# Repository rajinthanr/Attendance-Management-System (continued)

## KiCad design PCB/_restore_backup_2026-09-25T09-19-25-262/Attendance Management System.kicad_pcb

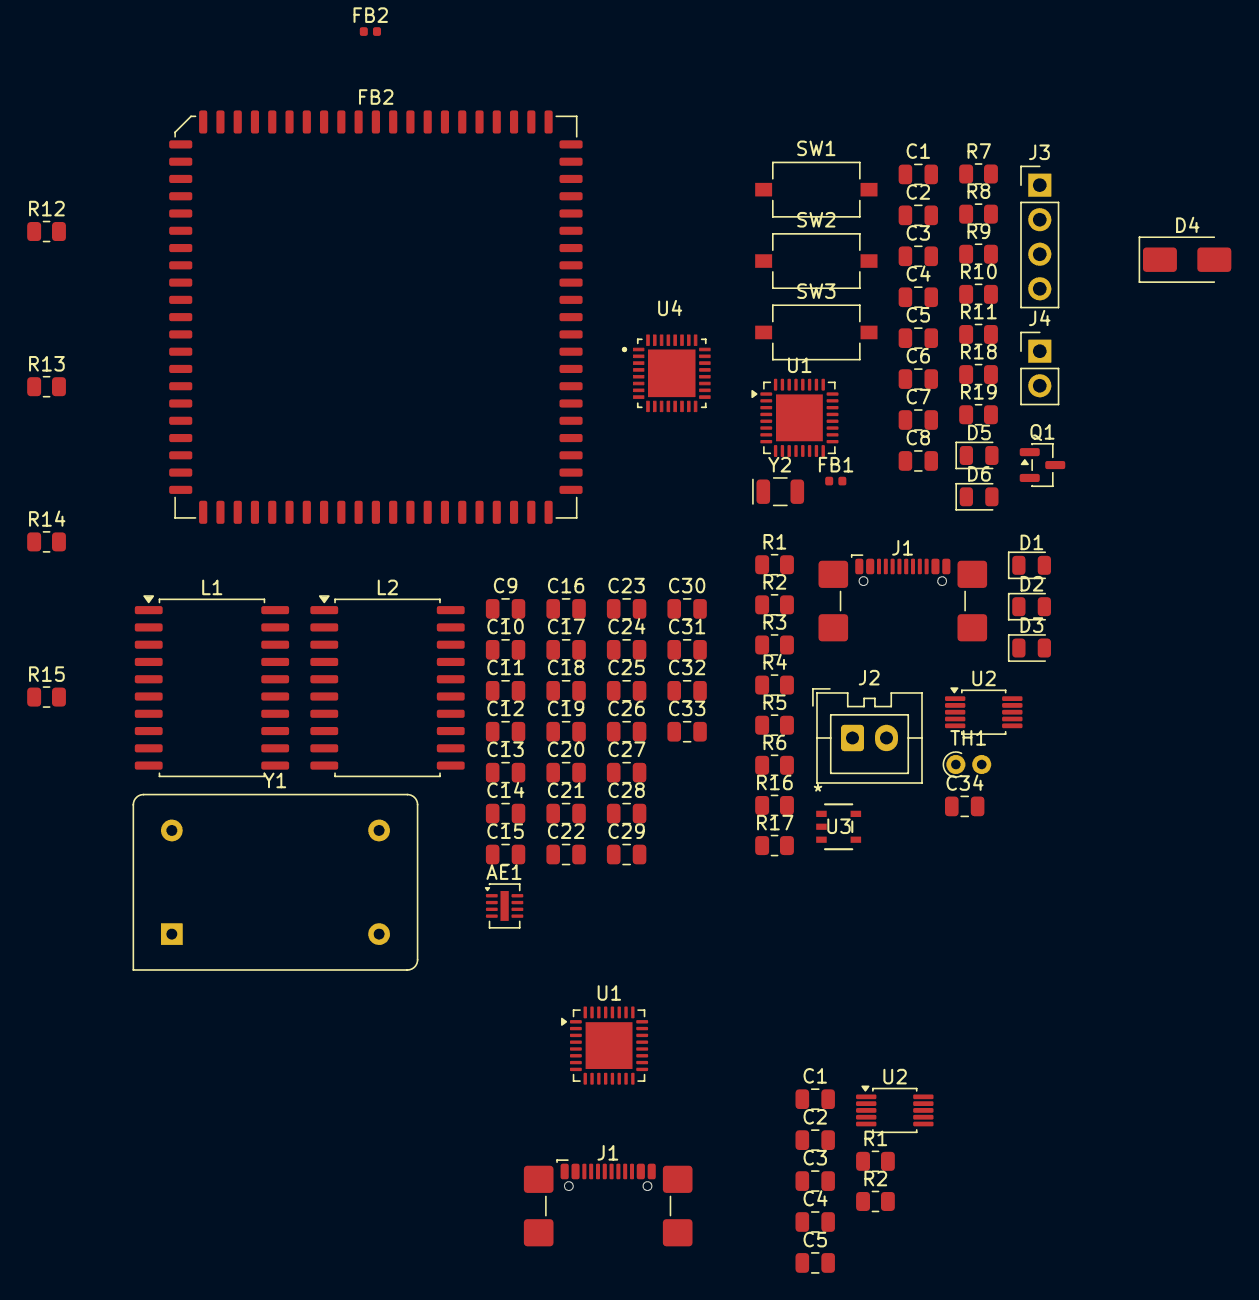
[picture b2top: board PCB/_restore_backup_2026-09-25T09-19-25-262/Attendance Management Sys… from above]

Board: 2 copper layers, 90 parts (0 on the bottom side), 59 nets, no tracks yet.

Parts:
AE1: Antenna; DFN-8-1EP_2x3mm_P0.5mm_EP0.61x2.2mm
C1, C1#2, C3, C3#2, C8, C34: 100n; C_0805_2012Metric
C2, C2#2: 4.7u; C_0805_2012Metric
C4, C4#2: 10n; C_0805_2012Metric
C5, C5#2: 1u; C_0805_2012Metric
C6, C7: 4.3p; C_0805_2012Metric
C9, C10: 15pF; C_0805_2012Metric
C11, C24, C25: 100nF; C_0805_2012Metric
C12, C13: 150 pF; C_0805_2012Metric
C14, C15: 100 pF; C_0805_2012Metric
C16, C17: 68 pF; C_0805_2012Metric
C18, C19: 270 pF; C_0805_2012Metric
C20, C21: 10uF; C_0805_2012Metric
C22, C23, C28, C29, C30: 100 nF; C_0805_2012Metric
C26, C27, C31, C32: 2.2uF; C_0805_2012Metric
C33: 1 uF; C_0805_2012Metric
D1, D5: RED; LED_0805_2012Metric
D2, D3, D6: GREEN; LED_0805_2012Metric
D4: SS14; D_SMA
FB1, FB2#2: FB 600 Ohm @ 100MHz; L_0402_1005Metric
FB2: 600 Ohm @ 100MHz; PLCC-84_29.3x29.3mm_P1.27mm
J1, J1#2: USB_C_Receptacle_USB2.0_16P; USB_C_Receptacle_GCT_USB4110
J2: BAT; JST_XA_B02B-XASK-1_1x02_P2.50mm_Vertical
J3: SW; PinHeader_1x04_P2.54mm_Vertical
J4: MOT; PinHeader_1x02_P2.54mm_Vertical
L1, L2: 470 nH; SOIC-20W_7.5x12.8mm_P1.27mm
Q1: AO3400A; SOT-23
R1, R1#2, R2, R2#2: 5K1; R_0805_2012Metric
R3, R4, R5, R9, R10: 470; R_0805_2012Metric
R6: 1K; R_0805_2012Metric
R7, R8, R11: 10K; R_0805_2012Metric
R12: 10k; R_0805_2012Metric
R13, R14: 1 KOhm; R_0805_2012Metric
R15: 1.5 KOhm; R_0805_2012Metric
R16, R18, R19: 4M7; R_0805_2012Metric
R17: 2M7; R_0805_2012Metric
SW1: RST; SW_Tactile_SPST_NO_Straight_CK_PTS636Sx25SMTRLFS
SW2: BOOT; SW_Tactile_SPST_NO_Straight_CK_PTS636Sx25SMTRLFS
SW3: KEY; SW_Tactile_SPST_NO_Straight_CK_PTS636Sx25SMTRLFS
TH1: Therm_NTC; R_Axial_DIN0204_L3.6mm_D1.6mm_P1.90mm_Vertical
U1, U1#2: STM32L432KCUx; QFN-32-1EP_5x5mm_P0.5mm_EP3.45x3.45mm
U2, U2#2: MCP73833-xxx-UN; MSOP-10_3x3mm_P0.5mm
U3: TPS7A0233PDBVR; SOT23_DBV_TEX-L
U4: ST25R3916-AQWT; QFN50P500X500X100-33N
Y1: 27.120 MHz; Oscillator_DIP-14
Y2: 32kHz; Crystal_SMD_EuroQuartz_EQ161-2Pin_3.2x1.5mm

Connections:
+3V3: C1.1, C1#2.1, C2.1, C2#2.1, C3.1, C3#2.1, C11.1, C21.1, C25.1, FB1.1, FB2.1, FB2#2.2, J3.1, R8.1, R12.1, SW2.2, U1.1 (VDD), U1.17 (VDD), U1#2.1 (VDD), U1#2.17 (VDD), U3.5 (OUT), U4.1 (VDD_IO), U4.10 (VDD_TX)
+5V: D1.2 (A), D2.2 (A), D3.2 (A), J1.A4 (VBUS), J1.A9 (VBUS), J1.B4 (VBUS), J1.B9 (VBUS), J1#2.A4 (VBUS), J1#2.A9 (VBUS), J1#2.B4 (VBUS), J1#2.B9 (VBUS), R18.1, U2.1 (V_{DD}), U2.2 (V_{DD})
/D+: J1.A6 (D+), J1.B6 (D+)
/D-: J1.A7 (D-), J1.B7 (D-)
/MCU/BAT_SENSE: C34.1, R16.2, R17.1, U1.13 (PA7), U1.30 (PB7)
/MCU/BOOT: R7.1, SW2.1, U1.31 (PH3)
/MCU/D+: J1#2.A6 (D+), J1#2.B6 (D+), U1.22 (PA12)
/MCU/D-: J1#2.A7 (D-), J1#2.B7 (D-), U1.21 (PA11)
/MCU/KEY: R8.2, SW3.2, U1.6 (PA0)
/MCU/LED_G: R10.1, U1.8 (PA2)
/MCU/LED_R: R9.1, U1.9 (PA3)
/MCU/LSC_IN: C7.2, U1.2 (PC14), Y2.2
/MCU/LSC_OUT: C6.1, U1.3 (PC15), Y2.1
/MCU/NFC_IRQ: U1.15 (PB1), U4.27 (IRQ)
/MCU/NFC_MISO: U1.27 (PB4), U4.32 (MISO/SDA)
/MCU/NFC_MOSI: U1.28 (PB5), U4.31 (MOSI)
/MCU/NFC_NSS: R12.2, U1.14 (PB0), U4.29 (~BSS)
/MCU/NFC_SCK: U1.26 (PB3), U4.30 (SCLK/SCL)
/MCU/SWCLK: J3.3, U1.24 (PA14)
/MCU/SWDIO: J3.2, U1.23 (PA13)
/MCU/VBUS: R18.2, R19.1, U1.19 (PA9)
/MCU/VIB_EN: Q1.1 (G), R11.1, U1.10 (PA4)
/MCU/nRST: C8.1, SW1.2, U1.4 (NRST)
/RFID/AN1: L1.1, U4.13 (RFO1)
/RFID/AN2: L2.1, U4.15 (RFO2)
/RFID/DC1: C20.1, C24.1, FB2.2, FB2#2.1, U4.8 (VDD)
/RFID/DC3: C22.1, C26.1, U4.9 (VDD_RF), U4.14 (VDD_DR)
/RFID/DC4: C23.1, C27.1, U4.11 (VDD_AM)
/RFID/DC5: C28.1, C31.1, U4.7 (VDD_A)
/RFID/DC6: C29.1, C32.1, U4.3 (VDD_D)
/RFID/DC7: C30.1, C33.1, U4.24 (AGDC)
/RFID/DR1: AE1.1 (A_1), C16.1, C18.1, R13.2, R15.1
/RFID/DR2: C17.1, C19.1, R14.2, R15.2
BAT+: D4.1 (K), J2.1, J4.1, R16.1, U2.9 (V_{BAT}), U2.10 (V_{BAT}), U3.1 (IN), U3.3 (EN)
GND: C1.2, C1#2.2, C2.2, C2#2.2, C3.2, C3#2.2, C4.2, C4#2.2, C5.2, C5#2.2, C6.2, C7.1, C8.2, C9.1, C10.2, C11.2, C12.2, C13.2, C18.2, C19.2, C20.2, C21.2, C22.2, C23.2, C24.2, C25.2, C26.2, C27.2, C28.2, C29.2, C30.2, C31.2, C32.2, C33.2, C34.2, D5.1 (K), D6.1 (K), J1.A1 (GND), J1.A12 (GND), J1.B1 (GND), J1.B12 (GND), J1.SH (SHIELD), J1#2.A1 (GND), J1#2.A12 (GND), J1#2.B1 (GND), J1#2.B12 (GND), J1#2.SH (SHIELD), J2.2, J3.4, Q1.2 (S), R1.2, R1#2.2, R2.2, R2#2.2, R6.2, R7.2, R11.2, R17.2, R19.2, SW1.1, SW3.1, TH1.2, U1.16 (VSS), U1.32 (VSS), U1.33 (VSS), U1#2.16 (VSS), U1#2.32 (VSS), U1#2.33 (VSS), U2.5 (V_{SS}), U3.2 (GND), U4.6 (GND_D), U4.12 (GND_DR), U4.16 (GND_DR), U4.20 (I2C_EN), U4.21 (VSS), U4.26 (GND_A), U4.33 (EXP)
unnamed: C12.1, C16.2, L1.2
unnamed: C13.1, C17.2, L2.2
unnamed: C14.2, R13.1
unnamed: C15.2, R14.1
unnamed: D1.1 (K), R3.1
unnamed: D2.1 (K), R4.1
unnamed: D3.1 (K), R5.1
unnamed: D4.2 (A), J4.2, Q1.3 (D)
unnamed: D5.2 (A), R9.2
unnamed: D6.2 (A), R10.2
unnamed: J1.A5 (CC1), J1#2.A5 (CC1), R1.1, R1#2.1
unnamed: J1.B5 (CC2), J1#2.B5 (CC2), R2.1, R2#2.1
unnamed: R6.1, U2.6 (PROG)
unnamed: R3.2, U2.3 (STAT1)
unnamed: R4.2, U2.4 (STAT2)
unnamed: TH1.1, U2.8 (THERM)
unnamed: U2#2.9 (V_{BAT}), U2#2.10 (V_{BAT})
unnamed: U2#2.1 (V_{DD}), U2#2.2 (V_{DD})
unnamed: R5.2, U2.7 (~PG)
unnamed: C14.1, U4.22 (RFI1)
unnamed: C15.1, U4.23 (RFI2)
unnamed: C9.2, U4.5 (XTI), Y1.1 (1_1)
unnamed: C10.1, U4.4 (XTO)
VDDA: C4.1, C4#2.1, C5.1, C5#2.1, FB1.2, U1.5 (VDDA), U1#2.5 (VDDA)

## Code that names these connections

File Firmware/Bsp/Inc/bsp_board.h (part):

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 *
 *  Pin   Signal            Function
 *  ----  ----------------  ---------------------------------------------------
 *  PC14  LSE_IN            32.768 kHz crystal. Keeps the RTC, and with it
 *  PC15  LSE_OUT           the CSV timestamps, running while the unit is off.
 *  PA0   PWR_BTN           WKUP1, the only Standby wake source. EXTI0 (both
 *                          edges) wakes the loop; the level is sampled there.
 *  PA1   --                Spare.
 *  PA2   LED_GREEN         Active high.
 *  PA3   LED_RED           Active high.
 *  PA4   VIB_EN            Vibration motor driver enable.
 *  PA5   --                Spare.
 *  PA6   --                Spare.
 *  PA7   BATT_SENSE        ADC1_IN12, 4.7M/2.7M divider off the cell.
 *  PA8   --                Spare.
 *  PA9   USB_VBUS          VBUS detect through R18/R19. EXTI9 (both edges)
 *                          wakes the loop; the level is sampled there.
 *  PA10  --                Spare.
 *  PA11  USB_DM            Fixed function.
 *  PA12  USB_DP            Fixed function.
 *  PA13  SWDIO             Debug. Left configured so the part stays attachable.
 *  PA14  SWCLK             Debug.
 *  PA15  PN532_NSS         Backup reader chip select, active low.
 *  PB0   NFC_NSS           ST25R3916 chip select, active low.
 *  PB1   NFC_IRQ           ST25R3916 interrupt, active high. EXTI1 (rising)
 *                          while the reader is in wake-up mode, otherwise
 *                          polled by bsp_nfc.c with the line masked.
 *  PB3   NFC_SCK           Shared SPI1 clock, AF5.
 *  PB4   NFC_MISO          Shared SPI1 input, AF5, pull-down.
 *  PB5   NFC_MOSI          Shared SPI1 output, AF5.
 *  PB6   PN532_IRQ         Backup reader interrupt, active low. Unused.
 *  PB7   PVD_IN            Same node as PA7; the PVD compares it to VREFINT.
 *  PH3   BOOT0             Strapped low.
 */
#ifndef BSP_BOARD_H
#define BSP_BOARD_H
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#define PIN_LED_RED         GPIO_PIN_3
#define PORT_LED_RED        GPIOA

#define PIN_VIB_EN          GPIO_PIN_4
#define PORT_VIB_EN         GPIOA

#define PIN_BATT_SENSE      GPIO_PIN_7
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#define PIN_USB_DP          GPIO_PIN_12
#define PORT_USB            GPIOA

#define PIN_PN532_NSS       GPIO_PIN_15
#define PORT_PN532_NSS      GPIOA

#define PIN_NFC_NSS         GPIO_PIN_0
#define PORT_NFC_NSS        GPIOB
#define PIN_NFC_IRQ         GPIO_PIN_1
#define PORT_NFC_IRQ        GPIOB
#define PIN_NFC_SCK         GPIO_PIN_3
#define PIN_NFC_MISO        GPIO_PIN_4
#define PIN_NFC_MOSI        GPIO_PIN_5
#define PORT_NFC_SPI        GPIOB
#define PIN_PN532_IRQ       GPIO_PIN_6
#define PORT_PN532_IRQ      GPIOB

#define PIN_PVD_IN          GPIO_PIN_7
#define PORT_PVD_IN         GPIOB

/** The power button shorts PA0 to ground. */
#define PWR_BTN_ACTIVE_LEVEL     GPIO_PIN_RESET

/** ST25R3916 IRQ is active high. */
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/* ------------------------------------------------------------------------ */

#define BSP_BATT_ADC            ADC1
#define BSP_BATT_ADC_CHANNEL    ADC_CHANNEL_12          /* PA7 */

/* ------------------------------------------------------------------------ */
/* Flash storage region                                                     */
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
